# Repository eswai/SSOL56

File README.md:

# 分割キーボードSSOL56

SSOL56は左右分割型の56キーのキーボードです。いろいろなコンセプトの検証のために作ったキーボードです。

## 特徴

- biacco42氏提唱のModuloアーキテクチャに準拠しています。ただし無線化には対応しません。
- Otholinearレイアウトをベースにしていますが、親指キーは自然に打てるレイアウトに変更しました。
- 一般的な19mmピッチより狭いキーピッチを試すために、ロープロファイルキースイッチとキーキャップを使用して、横18mm、縦17mmピッチで配置しています。Helix Picoと同じです。

## 設計

- biacco42氏のリファレンス設計を基にしており、使用している部品もTCA9555など、ほぼ同じです。
- Moduloアーキテクチャに忠実に従えば、TRRSはINT信号も含めた2個で1セットですが、今回は無線化する予定はなく、スペースも限られているので、INT信号は省略しました。
- Kailh low profileスイッチ専用です。ソケットに対応しています。
- 設計を容易にするためリバーシブル基板はやめ、また左右の基板を共通にするため、キーレイアウトは左右対称にしました。

## 写真

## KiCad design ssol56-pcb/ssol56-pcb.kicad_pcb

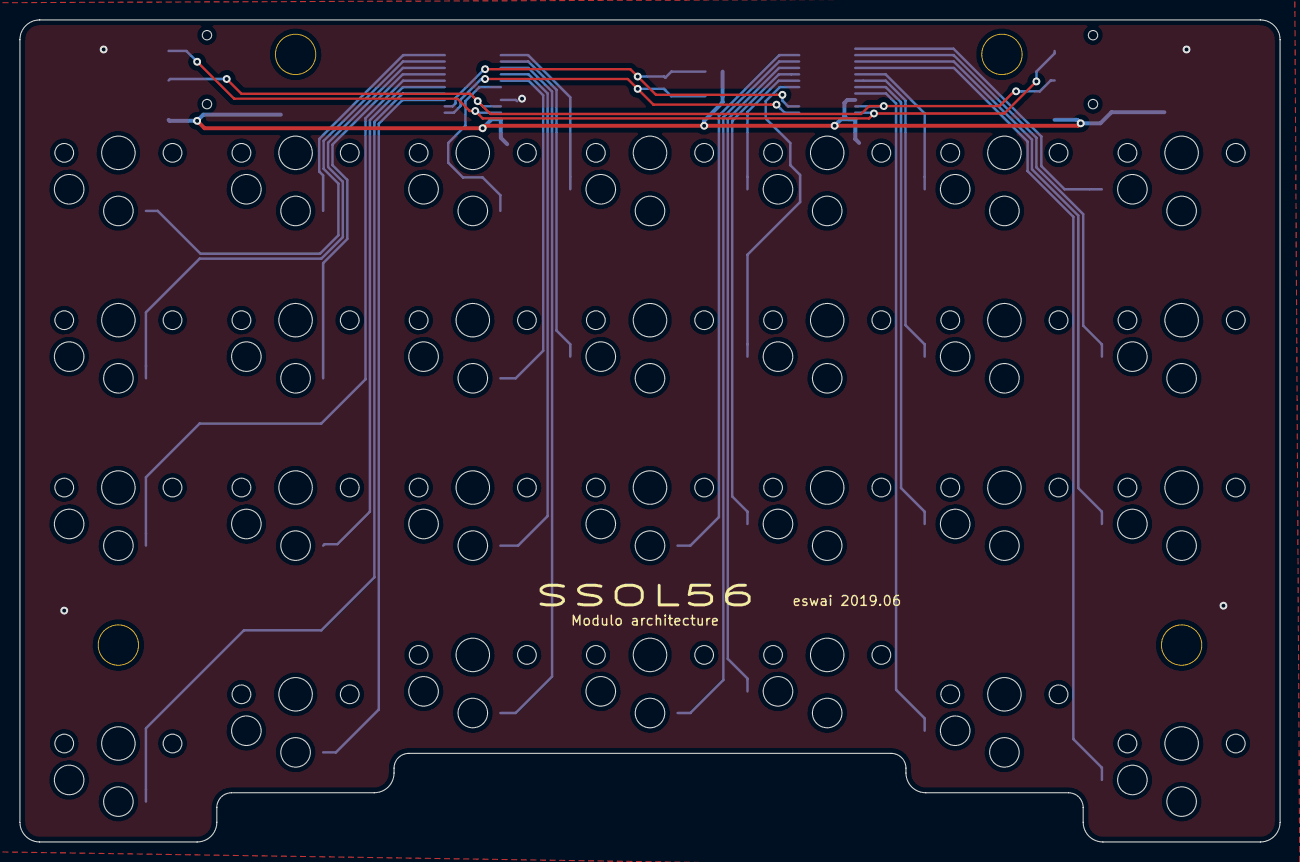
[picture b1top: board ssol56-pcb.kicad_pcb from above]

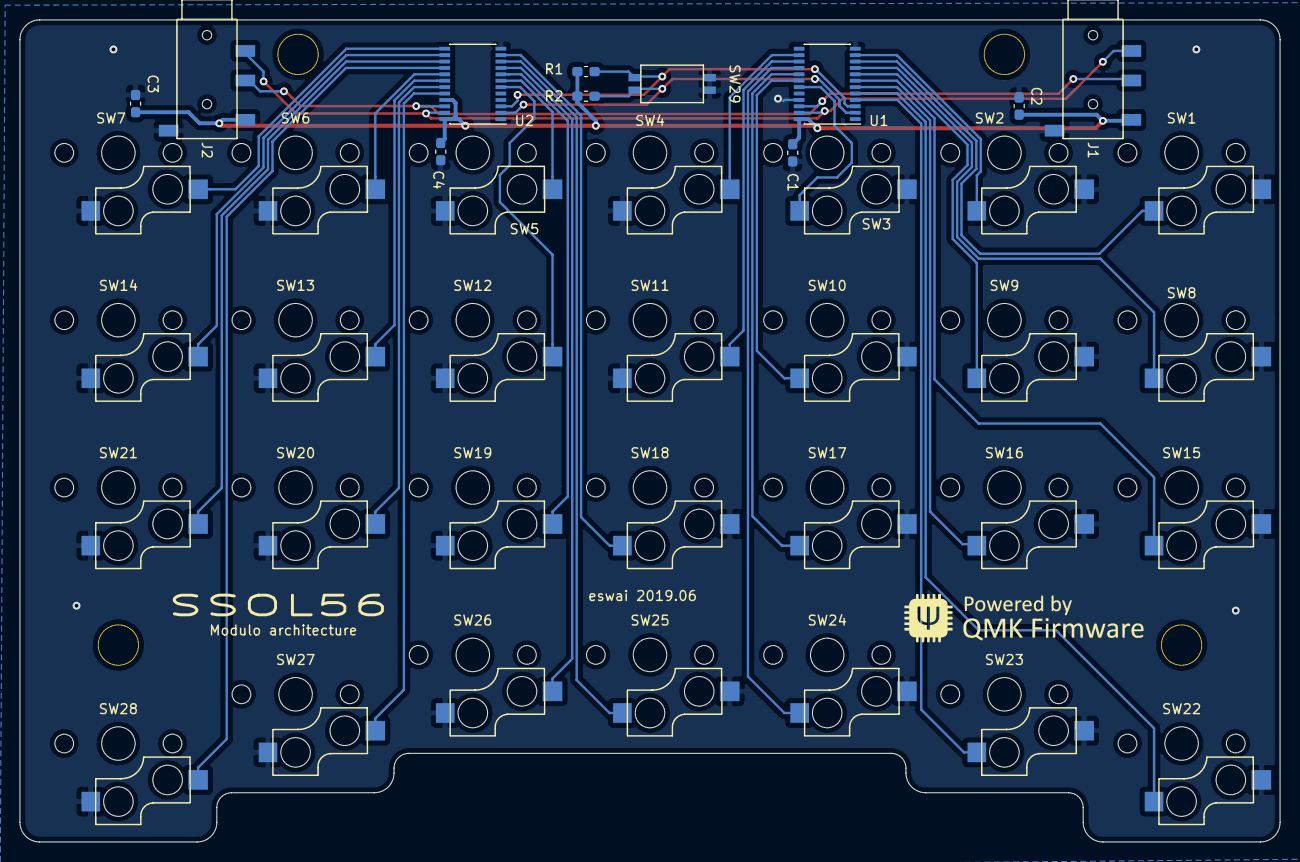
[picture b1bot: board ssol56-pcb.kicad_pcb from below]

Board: 2 copper layers, 128.0 x 83.5 mm, 43 parts (11 on the bottom side), 34 nets.

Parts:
C1, C2, C3, C4: C; C_0603_1608Metric_Pad1.05x0.95mm_HandSolder
H1, H2, H3, H4: MountingHole; HOLE
J1, J2: MJ-4PP-9; TRRS_SMD_PJ320_single
R1, R2: R; R_0603_1608Metric_Pad1.05x0.95mm_HandSolder
SW1, SW2, SW3, SW4, SW5, SW6, SW7, SW8, SW9, SW10, SW11, SW12, SW13, SW14, SW15, SW16, SW17, SW18, SW19, SW20, SW21, SW22, SW23, SW24, SW25, SW26, SW27, SW28: SW_PUSH; CherryMX_Choc_Hotswap_copy
SW29: SW_DIP_x02; DipSwitch
U1, U2: TCA9555PWR; TSSOP-24_4.4x7.8mm_P0.65mm

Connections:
A1: R2.1, SW29.2, U1.2, U2.2
A2: R1.2, SW29.1, U1.3, U2.3
GND: C1.2, C2.2, C3.2, C4.2, J1.A, J2.A, SW1.1, SW2.1, SW3.1, SW4.2, SW5.2, SW6.2, SW7.2, SW8.1, SW9.1, SW10.1, SW11.2, SW12.2, SW13.2, SW14.2, SW15.1, SW16.1, SW17.1, SW18.1, SW19.2, SW20.2, SW21.2, SW22.1, SW23.1, SW24.1, SW25.1, SW26.2, SW27.2, SW28.2, SW29.3, SW29.4, U1.12, U1.21, U2.12
SCL: J1.C, J2.C, U1.22, U2.22
SDA: J1.B, J2.B, U1.23, U2.23
SW1: SW1.2, U1.10
SW2: SW2.2, U1.11
SW3: SW3.2, U1.19
SW4: SW4.1, U1.14
SW5: SW5.1, U2.7
SW6: SW6.1, U2.17
SW7: SW7.1, U2.13
SW8: SW8.2, U1.9
SW9: SW9.2, U1.8
SW10: SW10.2, U1.18
SW11: SW11.1, U1.15
SW12: SW12.1, U2.6
SW13: SW13.1, U2.18
SW14: SW14.1, U2.14
SW15: SW15.2, U1.7
SW16: SW16.2, U1.6
SW17: SW17.2, U1.17
SW18: SW18.2, U2.11
SW19: SW19.1, U2.8
SW20: SW20.1, U2.19
SW21: SW21.1, U2.15
SW22: SW22.2, U1.5
SW23: SW23.2, U1.4
SW24: SW24.2, U1.16
SW25: SW25.2, U2.10
SW26: SW26.1, U2.9
SW27: SW27.1, U2.20
SW28: SW28.1, U2.16
VCC: C1.1, C2.1, C3.1, C4.1, J1.D, J2.D, R1.1, R2.2, U1.24, U2.21, U2.24

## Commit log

2019-06-30 Inital commit
2019-06-30 Photos
